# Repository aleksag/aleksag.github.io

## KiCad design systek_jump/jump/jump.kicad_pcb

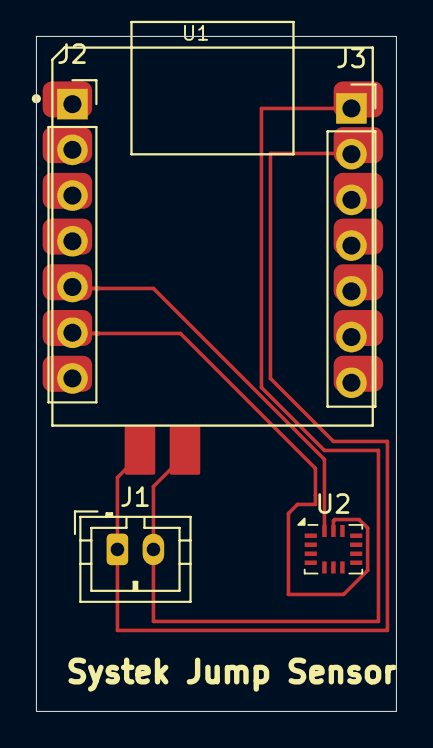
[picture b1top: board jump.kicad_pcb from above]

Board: 2 copper layers, 20.0 x 37.5 mm, 5 parts (0 on the bottom side), 16 nets.

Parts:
J1: Conn_01x02_Pin; JST_PH_B2B-PH-K_1x02_P2.00mm_Vertical
J2, J3: Conn_01x07_Socket; PinSocket_1x07_P2.54mm_Vertical
U1: SeeeduinoXIAO; MOUDLE14P-2.54-21X17.8MM
U2: BMI160; Bosch_LGA-14_3x2.5mm_P0.5mm

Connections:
unnamed: J2.1, U1.1 (PA02_A0_D0)
unnamed: J2.2, U1.2 (PA4_A1_D1)
unnamed: J2.3, U1.3 (PA10_A2_D2)
unnamed: J2.4, U1.4 (PA11_A3_D3)
unnamed: J2.5, U1.5 (PA8_A4_D4_SDA)
unnamed: J2.6, U1.6 (PA9_A5_D5_SCL)
unnamed: J2.7, U1.7 (PB08_A6_D6_TX)
unnamed: J3.1, U1.14 (5V)
unnamed: J3.2, U1.13 (GND)
unnamed: J3.3, U1.12 (3V3)
unnamed: J3.4, U1.11 (PA6_A10_D10_MOSI)
unnamed: J3.5, U1.10 (PA5_A9_D9_MISO)
unnamed: J3.6, U1.9 (PA7_A8_D8_SCK)
unnamed: J3.7, U1.8 (PB09_A7_D7_RX)
unnamed: U2.6 (GNDIO), U2.7 (GND)
unnamed: U2.5 (VDDIO), U2.8 (VDD)

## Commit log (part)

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2023-09-07 Indexfile
2023-09-07 Fikser typo
2023-09-07 Fikser submit og typo
2023-09-07 Formatering
2023-09-07 Fikser på keyup
2023-09-18 Teppetapet.mp3
2023-09-18 Flere klipp
2024-02-18 Lagt til creative
2024-02-18 POC systek aktivitetskalender
2024-02-29 Flashcards
2024-02-29 Driter i å hente fra nettsida
2024-02-29 Litt justeringer
2024-03-02 Gjetteversjon
2024-03-13 Streker
2024-03-17 Working on both boards
2024-03-25 Sensorboard
2024-03-25 Oppdaterer
2024-03-25 Body
2024-03-25 Added fillet to board lid
2024-04-15 Forsøk
2024-04-15 Rendra ut bitsholder
2024-04-15 Demo tinkercad
2024-05-23 Vits.no
2024-05-29 pcb-shit
2024-06-05 Final checks
2024-09-16 Merge
2024-09-16 Prøver med cors-jukking
2024-09-17 Cors funka ikke
2024-09-17 Tekst
2024-09-17 Random dropdown
2024-09-17 Fjerner roboter
2024-09-17 Trimmer navn fra systek.no
2024-09-17 Lagt på juggel
2024-09-29 WIP statistikk
2024-09-29 Fjerner no console-logging
2024-09-29 Reset statistics fix
2024-09-29 Kan velge antall
2024-09-29 oppdaterer statistikk litt oftere
2024-10-15 jingle
2024-10-30 Breathe
2024-10-30 Sentrerer
2024-12-13 Oppdaterer ansattlista
2024-12-13 Fjerner robot
2025-02-03 Karlfix
2025-02-22 FUNGERENDE KNAPPER!
2025-02-23 Fungerende
2025-02-23 Fungerende scoreboard
2025-03-04 Index for scorecard
2025-03-04 Renamet knapp
2025-03-09 Scoreboard fungerer
2025-03-09 Fungerende verjson med scoreboard og bedre rng
2025-03-10 Oppdatert ansatte
2025-03-22 Støtter reset og volumsetting
2025-03-22 Lagt til connect og reset-funksjonalitet
2025-03-22 Funker
2025-04-07 Bugfix og readme
2025-05-08 Ny dump av folk
2025-06-10 Feedbutton ha
2025-10-28 Brevdue
2025-10-28 skalerer
2025-10-29 On hover
2026-01-15 Fikser no prosentgreier, takk Karl
2026-06-13 Flashcards2.0
